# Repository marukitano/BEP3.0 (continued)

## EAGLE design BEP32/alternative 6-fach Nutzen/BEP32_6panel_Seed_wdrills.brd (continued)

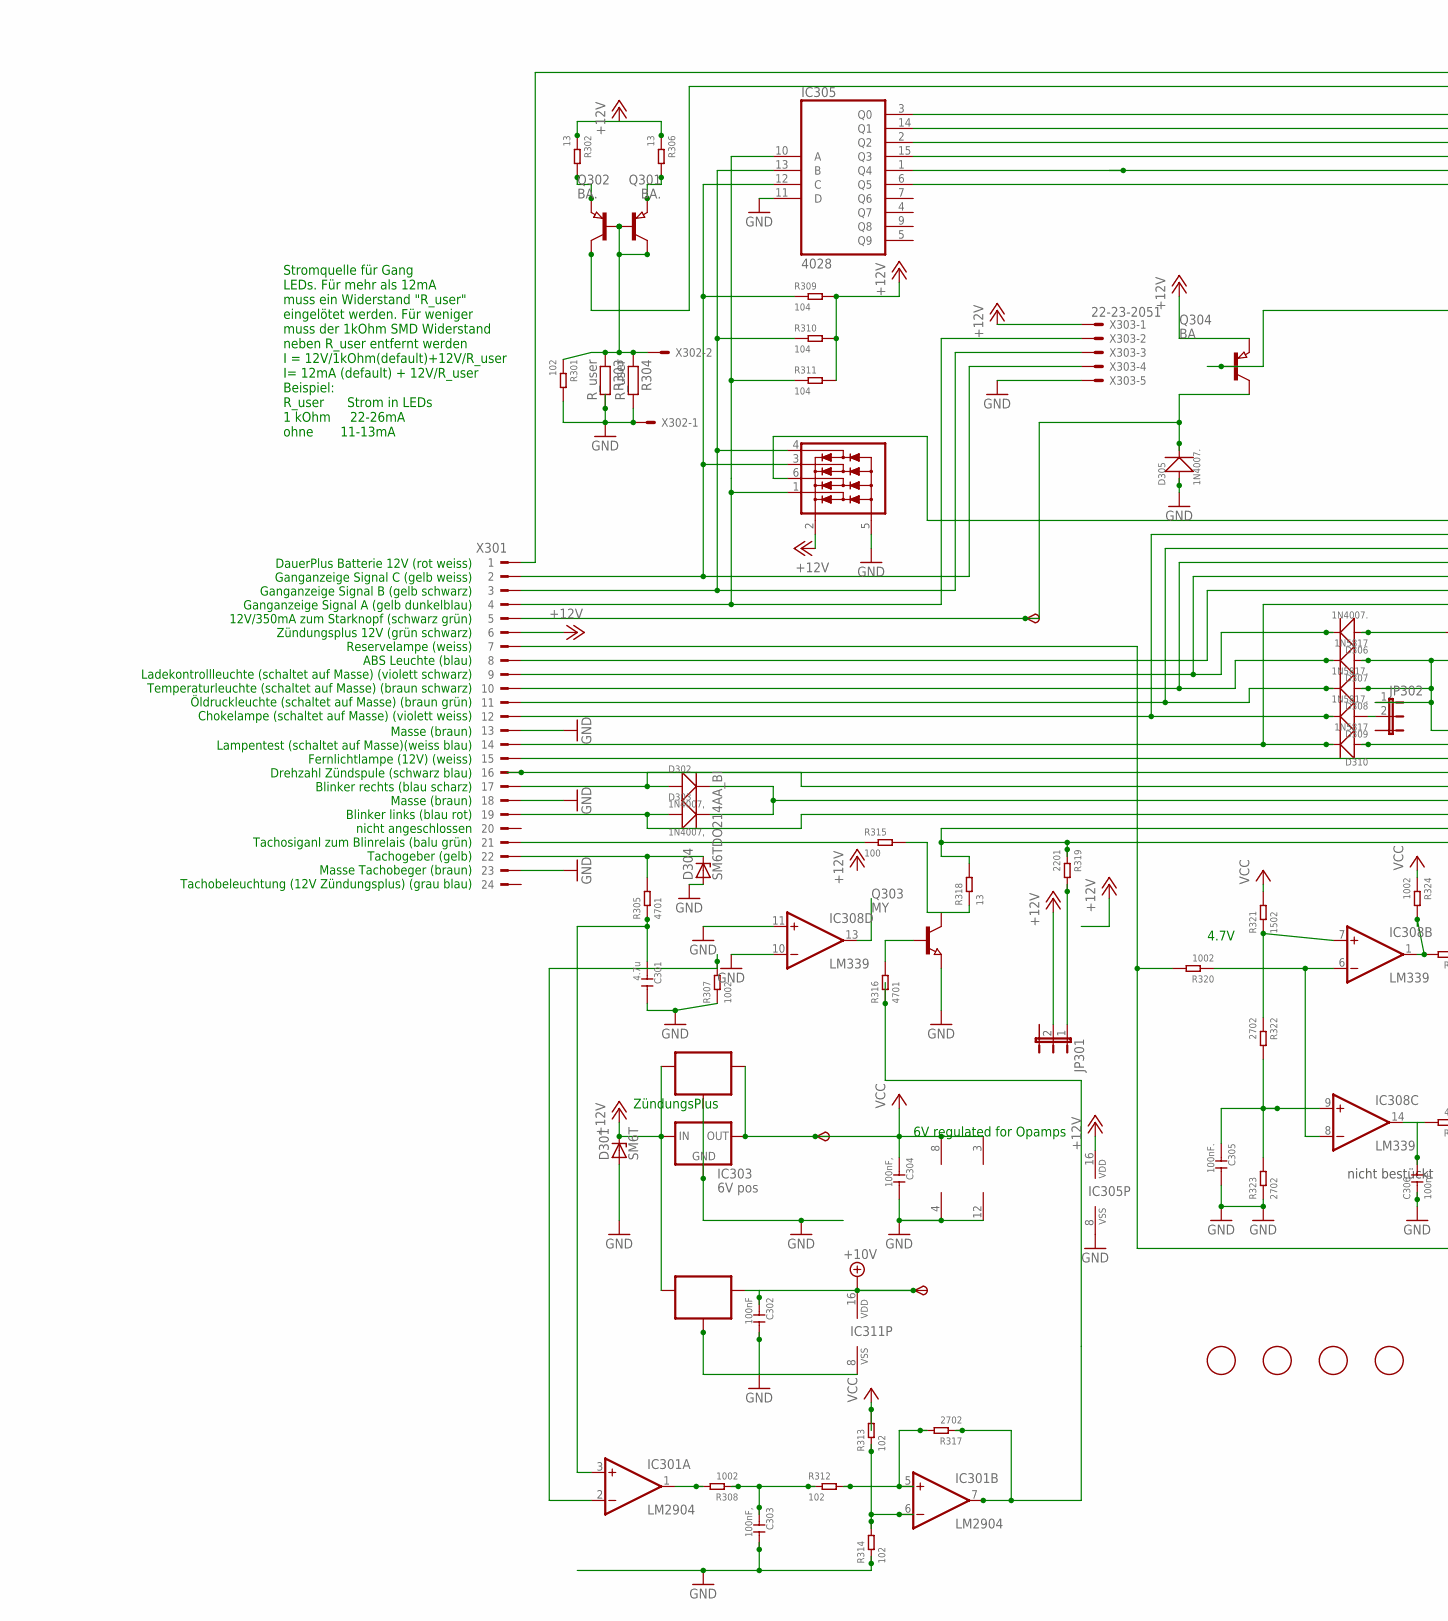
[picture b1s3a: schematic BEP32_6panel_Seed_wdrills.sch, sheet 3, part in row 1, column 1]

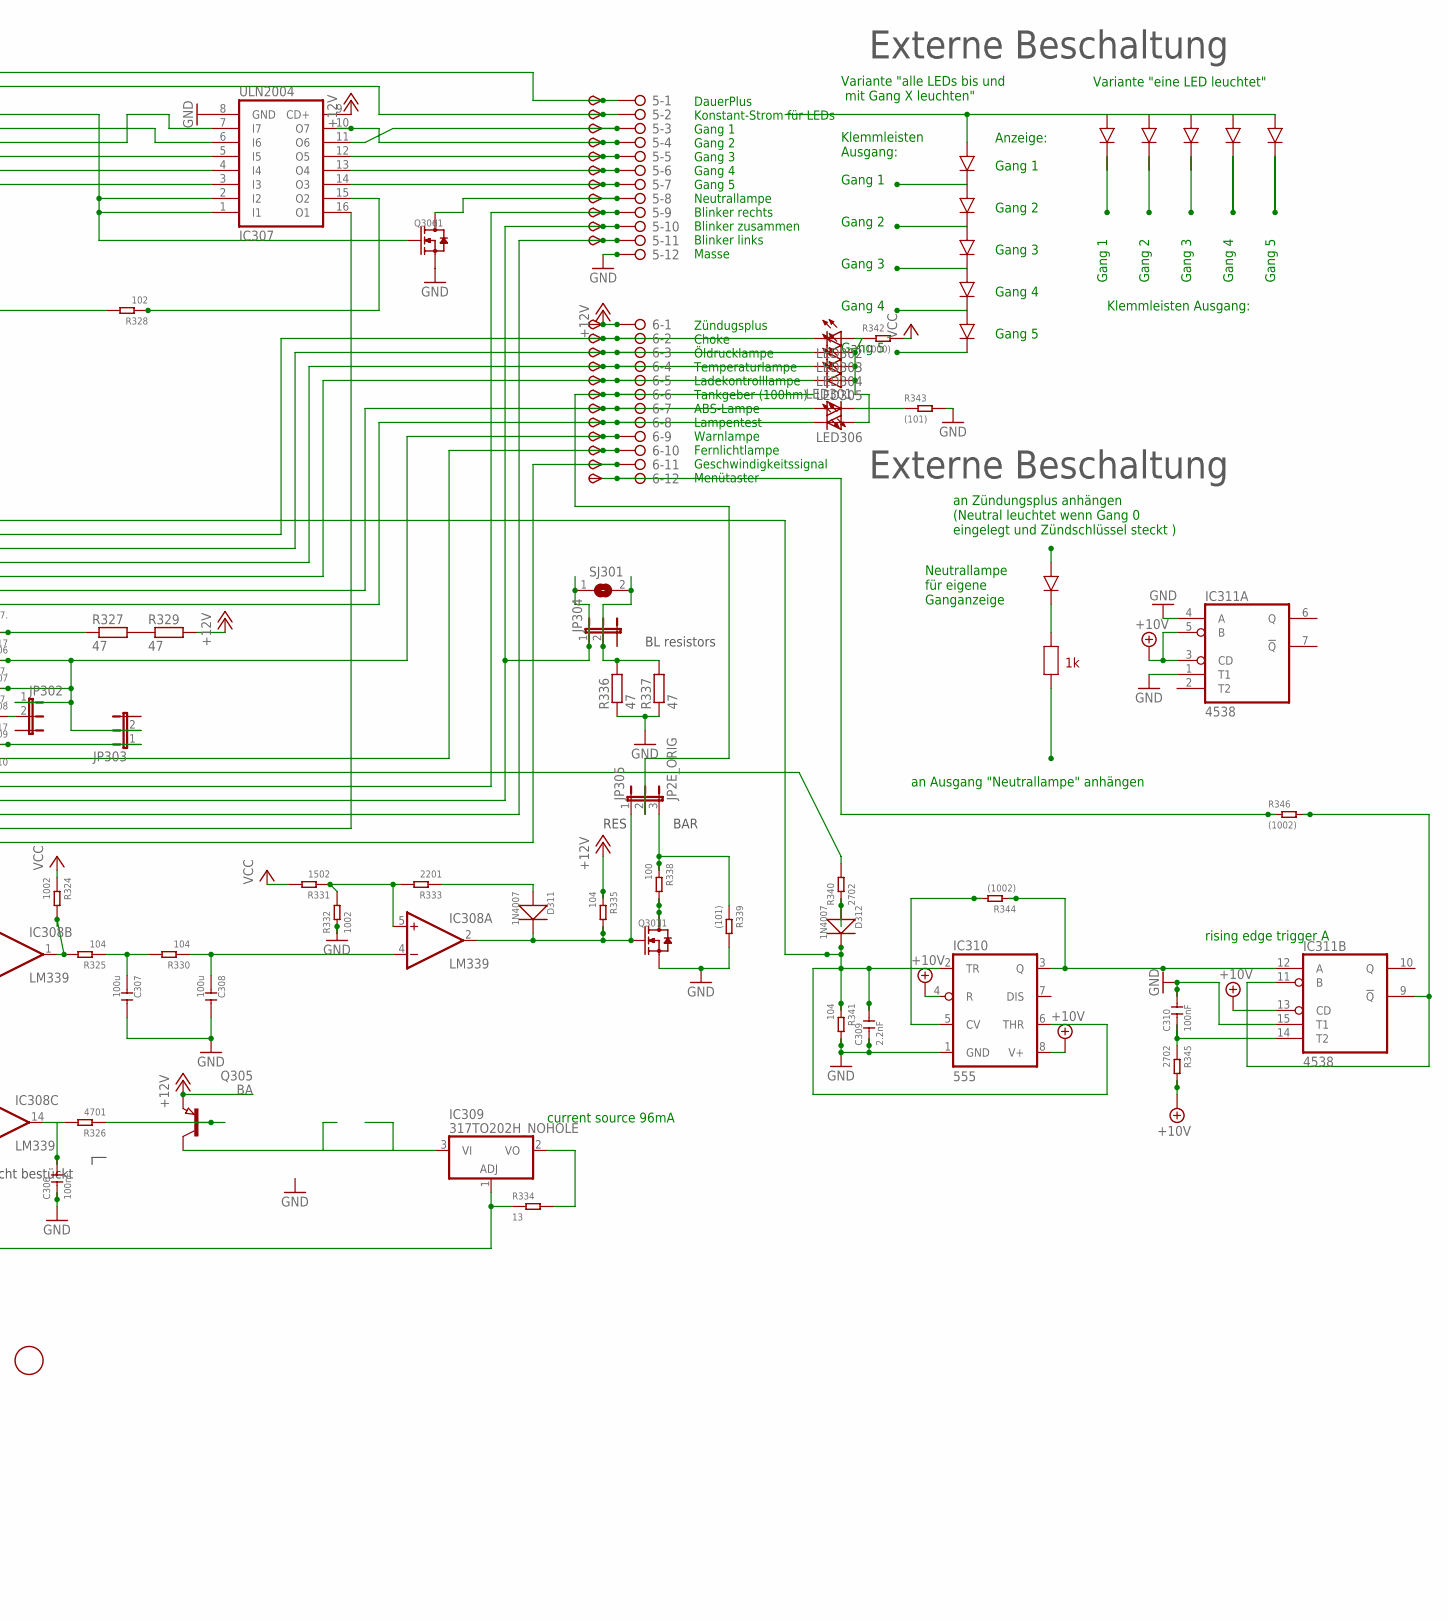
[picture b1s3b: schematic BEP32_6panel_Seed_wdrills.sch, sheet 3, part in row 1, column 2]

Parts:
5, 6: 2081-1132; 12-PIN
6V301, 10V301: TPSB2.0; B2.0
C301: 4.7u; C0805
C302, C310: 100nF; C0805
C303, C304: 100nF,; C0805
C305, C306: 100nF.; C0805
C307, C308: 100u; C1206
C309: 2.2nF; C0805
D301: SM6T; DO214AA
D302, D303: 1N4007,; DO-214AC
D304: SM6TDO214AA_BI; DO214AA_BI
D305, D306: 1N4007.; DO-214AC
D307, D310: 1N5817; DO-214AC_SLIM
D308, D309: 1N5817.; DO-214AC_SLIM
D311, D312: 1N4007; DO-214AC
FID301, FID302, FID303, FID304: FIDUCIAL; FIDUCIAL_1MM
IC301: LM2904; SO08
IC302: 78L06; SOT89_ROUND
IC303: 6V pos; 78LXX
IC304: 78L10; SOT89_ROUND
IC305: 4028; SO16
IC306: NUP4304SOT457_R; SOT457R_PHILIPS
IC307: ULN2004; SO16
IC308: LM339; SO14
IC309: 317TO202H_NOHOLE; TO220H_NOHOLE
IC310: 555; SO08
IC311: 4538; SO16
JP301, JP302, JP303, JP304: JP2EJP2_SMALLPADS; JP2_SMALLPADS
JP305: JP2E_ORIG; JP2_ORIG_SMALLPADS
LED301, LED302, LED303, LED304, LED305, LED306: LEDLD260; LD260
Q301, Q302: BA.; SOT89
Q303: MY; SOT89
Q304, Q305: BA; SOT89
Q306, Q307: J1; SOT-23
R301, R312, R313, R314, R328: 102; R0805
R302, R306, R318, R334: 13; R1206
R303, R304: R_user; R0805
R305, R316, R326: 4701; R0805
R307, R308, R320, R324, R332: 1002; R0805
R309, R310, R311, R325, R330, R335, R341: 104; R0805
R315, R338: 100; R0805
R317, R322, R323, R340, R345: 2702; R0805
R319, R333: 2201; R0805
R321, R331: 1502; R0805
R327, R329, R336, R337: 47; V235/17_1MM
R339, R343: (101); R0805
R342: (1000); R0805
R344, R346: (1002); R0805
SJ301: SJ
START301: TPSB2.0; B2.0
TP47, TP48, TP49, TP50, TP51, TP52, TP53, TP54, TP55, TP56, TP57, TP58, TP59, TP60, TP61, TP62, TP63, TP64, TP66, TP67, TP68, TP69: TPSB2.0; B2.0
TP65: TPSB1,27; B1,27
X301: CON_BMWV2; 24-PIN_V2
X302: 22-23-2021
X303: 22-23-2051

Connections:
+10V: 10V301.TP, C302.1, IC304.1 (OUT), IC310.4 (R), IC310.8 (V+), IC311.3 (CD), IC311.5 (B), IC311.13 (CD), IC311.16 (VDD), R345.2; also elsewhere on the board
+12V: 6.1, D301.C, IC302.3 (IN), IC303.IN, IC304.3 (IN), IC305.16 (VDD), IC306.2 (V+), IC307.9 (CD+), JP301.2, Q304.3 (E), Q305.3 (E), R302.1, R306.1, R309.2, R310.2, R311.2, R329.2, R335.1, TP68.TP, X301.6, X303.1; also elsewhere on the board
+12V3: IC301.7 (OUT), R316.1, R317.1
GND: 5.12, C301.2, C302.2, C303.2, C304.2, C305.2, C306.1, C307.2, C308.2, C309.1, C310.2, D301.A, D304.A, D305.1 (+), IC301.4 (V-), IC302.2 (GND), IC302.2@1 (GND), IC303.GND, IC304.2 (GND), IC304.2@1 (GND), IC305.8 (VSS), IC305.11 (D), IC306.5 (V-), IC307.8 (GND), IC308.10 (-IN), IC308.11 (+IN), IC308.12 (GND), IC310.1 (GND), IC311.1 (T1), IC311.4 (A), IC311.8 (VSS), IC311.15 (T1), Q303.3 (E), Q306.2 (S), Q307.2 (S), R301.2, R303.2, R304.2, R307.1, R314.1, R323.1, R332.1, R336.1, R337.1, R339.2, R341.2, R343.2, X301.13, X301.18, X301.23, X302.1, X303.5; also elsewhere on the board
unnamed: R327.2, R329.1
unnamed: 6.9, D307.1 (+), D308.1 (+), JP302.1, JP303.2, TP65.TP
unnamed: IC305.10 (A), IC306.1 (D1), R311.1, X301.4, X303.2
unnamed: IC305.13 (B), IC306.4 (D4), R310.1, X301.3, X303.3
unnamed: D305.2 (-), Q304.2 (C), START301.TP, X301.5
unnamed: IC305.12 (C), IC306.3 (D3), R309.1, X301.2, X303.4
unnamed: 6.7, LED301.A, TP63.TP, X301.8
unnamed: 6.2, D309.2 (-), LED302.K (C), TP58.TP, X301.12
unnamed: 6.3, D308.2 (-), LED303.K (C), TP59.TP, X301.11
unnamed: 6.4, D307.2 (-), LED304.K (C), TP60.TP, X301.10
unnamed: 6.8, D310.2 (-), LED306.K (C), TP64.TP, X301.14
unnamed: 5.9, D302.1 (+), TP55.TP, X301.17
unnamed: 5.11, D303.1 (+), TP57.TP, X301.19
unnamed: D304.C, R305.2, X301.22
unnamed: C301.1, IC301.3 (+IN), R305.1
unnamed: 6.11, IC307.16 (O1), R318.2, R319.1, TP67.TP
unnamed: IC308.1 (OUT), R324.2, R325.2
unnamed: C307.1, R325.1, R330.2
unnamed: C308.1, IC308.4 (-IN), R330.1
unnamed: IC308.5 (+IN), R331.1, R332.2, R333.2
unnamed: D311.1 (+), R333.1
unnamed: C305.1, IC308.9 (+IN), R322.2, R323.2
unnamed: C306.2, IC308.14 (OUT), R326.2
unnamed: Q305.1 (B), R326.1
unnamed: IC305.2 (Q2), IC307.7 (I7)
unnamed: 5.5, IC307.12 (O5), TP51.TP
unnamed: IC305.1 (Q4), IC307.4 (I4)
unnamed: 5.8, Q306.3 (D), TP54.TP
unnamed: 6.10, TP66.TP, X301.15
unnamed: 6.5, D306.2 (-), LED305.K (C), TP61.TP, X301.9
unnamed: D306.1 (+), R327.1
unnamed: IC305.6 (Q5), IC307.3 (I3)
unnamed: 5.4, IC307.10 (O7), TP50.TP
unnamed: IC309.1 (ADJ), R320.2, R334.1, X301.7
unnamed: IC308.6 (-IN), IC308.8 (-IN), R320.1
unnamed: 5.2, Q301.2 (C), TP48.TP
unnamed: 5.1, TP47.TP, X301.1
unnamed: R340.2, X301.16
unnamed: IC305.15 (Q3), IC307.5 (I5)
unnamed: 5.6, IC307.13 (O4), TP52.TP
unnamed: 5.7, IC307.14 (O3), TP53.TP
unnamed: 6.6, JP305.2, TP62.TP
unnamed: LED301.K (C), R343.1
unnamed: LED302.A, LED303.A, LED304.A, LED305.A, LED306.A, R342.1
unnamed: Q304.1 (B), R328.2
unnamed: IC305.3 (Q0), IC307.1 (I1), IC307.2 (I2), Q306.1 (G)
unnamed: IC305.14 (Q1), IC307.6 (I6)
unnamed: 5.3, IC307.11 (O6), TP49.TP
unnamed: Q301.1 (B), Q302.1 (B), Q302.2 (C), R301.1, R303.1, R304.1, X302.2
unnamed: Q301.3 (E), R302.2
unnamed: Q302.3 (E), R306.2
unnamed: IC308.7 (+IN), R321.1, R322.1
unnamed: IC301.2 (-IN), R307.2
unnamed: Q303.1 (B), R316.2
unnamed: Q307.3 (D), R338.2
unnamed: IC309.2 (VO), R334.2
unnamed: IC309.3 (VI), Q305.2 (C)
unnamed: C309.2, D312.2 (-), IC306.6 (D2), IC310.2 (TR), IC310.6 (THR), R341.1
unnamed: IC310.5 (CV), R344.2
unnamed: IC310.3 (Q), IC311.12 (A), R344.1
unnamed: D312.1 (+), R340.1
unnamed: 5.10, D302.2 (-), D303.2 (-), JP304.1, SJ301.1, TP56.TP
unnamed: JP304.2, R336.2, R337.2, SJ301.2
unnamed: IC311.9 (!Q), IC311.11 (B), R346.2
unnamed: C310.1, IC311.14 (T2), R345.1
unnamed: JP301.1, R319.2
unnamed: IC307.15 (O2), R328.1
unnamed: 6.12, R346.1, TP69.TP
unnamed: D309.1 (+), JP302.2
unnamed: D311.2 (-), IC308.2 (OUT), JP305.1, Q307.1 (G), R335.2
unnamed: IC301.1 (OUT), R308.2
unnamed: C303.1, R308.1, R312.1
unnamed: IC301.5 (+IN), R312.2, R317.2
unnamed: IC301.6 (-IN), R313.1, R314.2
unnamed: D310.1 (+), JP303.1
unnamed: JP305.3, R338.1, R339.1
unnamed: R315.1, X301.21
unnamed: Q303.2 (C), R315.2, R318.1
VCC: 6V301.TP, C304.1, IC301.8 (V+), IC302.1 (OUT), IC303.OUT, IC308.3 (V+), R313.2, R321.2, R324.1, R331.2, R342.2; also elsewhere on the board

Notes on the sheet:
6V regulated for Opamps
current source 96mA
ZündungsPlus
Zündugsplus Choke Öldrucklampe Temperaturlampe Ladekontrolllampe Tankgeber (100hm) ABS-Lampe Lampentest Warnlampe Fernlichtlampe Geschwindigkeitssignal Menütaster
DauerPlus Konstant-Strom für LEDs Gang 1 Gang 2 Gang 3 Gang 4 Gang 5 Neutrallampe Blinker rechts Blinker zusammen Blinker links Masse
DauerPlus Batterie 12V (rot weiss) Ganganzeige Signal C (gelb weiss) Ganganzeige Signal B (gelb schwarz) Ganganzeige Signal A (gelb dunkelblau) 12V/350mA zum Starknopf (schwarz grün) Zündungsplus 12V (grün schwarz) Reservelampe (weiss) ABS Leuchte (blau) Ladekontrollleuchte (schaltet auf Masse) (vi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
Masse (braun) Lampentest (schaltet auf Masse)(weiss blau) Fernlichtlampe (12V) (weiss) Drehzahl Zündspule (schwarz blau) Blinker rechts (blau scharz) Masse (braun) Blinker links (blau rot) nicht angeschlossen Tachosiganl zum Blinrelais (balu grün) Tachogeber (gelb) Masse Tachobeger (braun) Tachobel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
4.7V
Stromquelle für Gang LEDs. Für mehr als 12mA muss ein Widerstand "R_user" eingelötet werden. Für weniger muss der 1kOhm SMD Widerstand neben R_user entfernt werden I = 12V/1kOhm(default)+12V/R_user I= 12mA (default) + 12V/R_user Beispiel: R_user Strom in LEDs 1 kOhm 22-26mA ohne 11-13mA
Gang 1
Gang 2
Gang 3
Gang 4
Gang 5
Variante "eine LED leuchtet"
Variante "alle LEDs bis und mit Gang X leuchten"
Klemmleisten Ausgang:
Klemmleisten Ausgang:
an Zündungsplus anhängen (Neutral leuchtet wenn Gang 0 eingelegt und Zündschlüssel steckt )
an Ausgang "Neutrallampe" anhängen
Neutrallampe für eigene Ganganzeige
Externe Beschaltung
Anzeige:
nicht bestückt
rising edge trigger A
BAR
RES
BL resistors

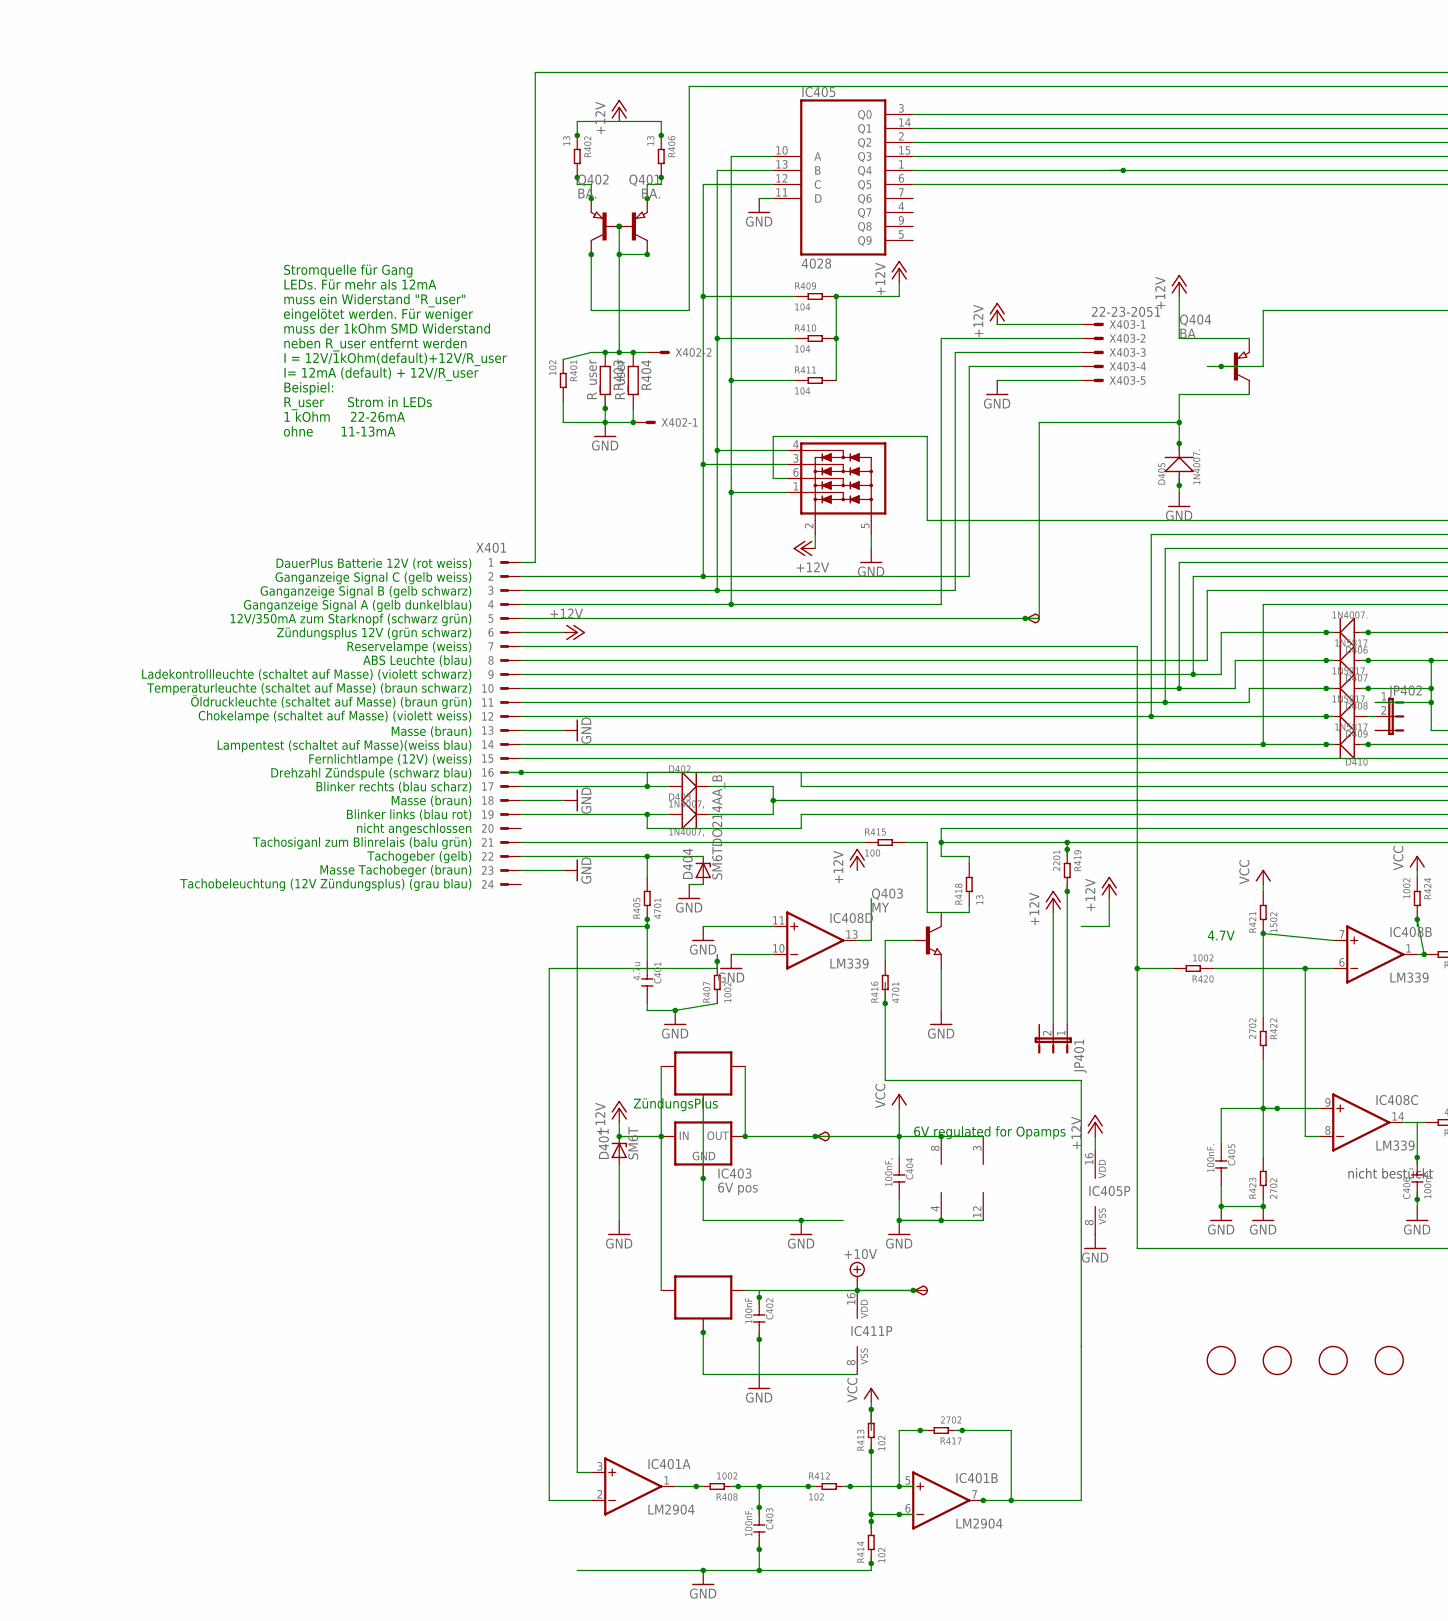
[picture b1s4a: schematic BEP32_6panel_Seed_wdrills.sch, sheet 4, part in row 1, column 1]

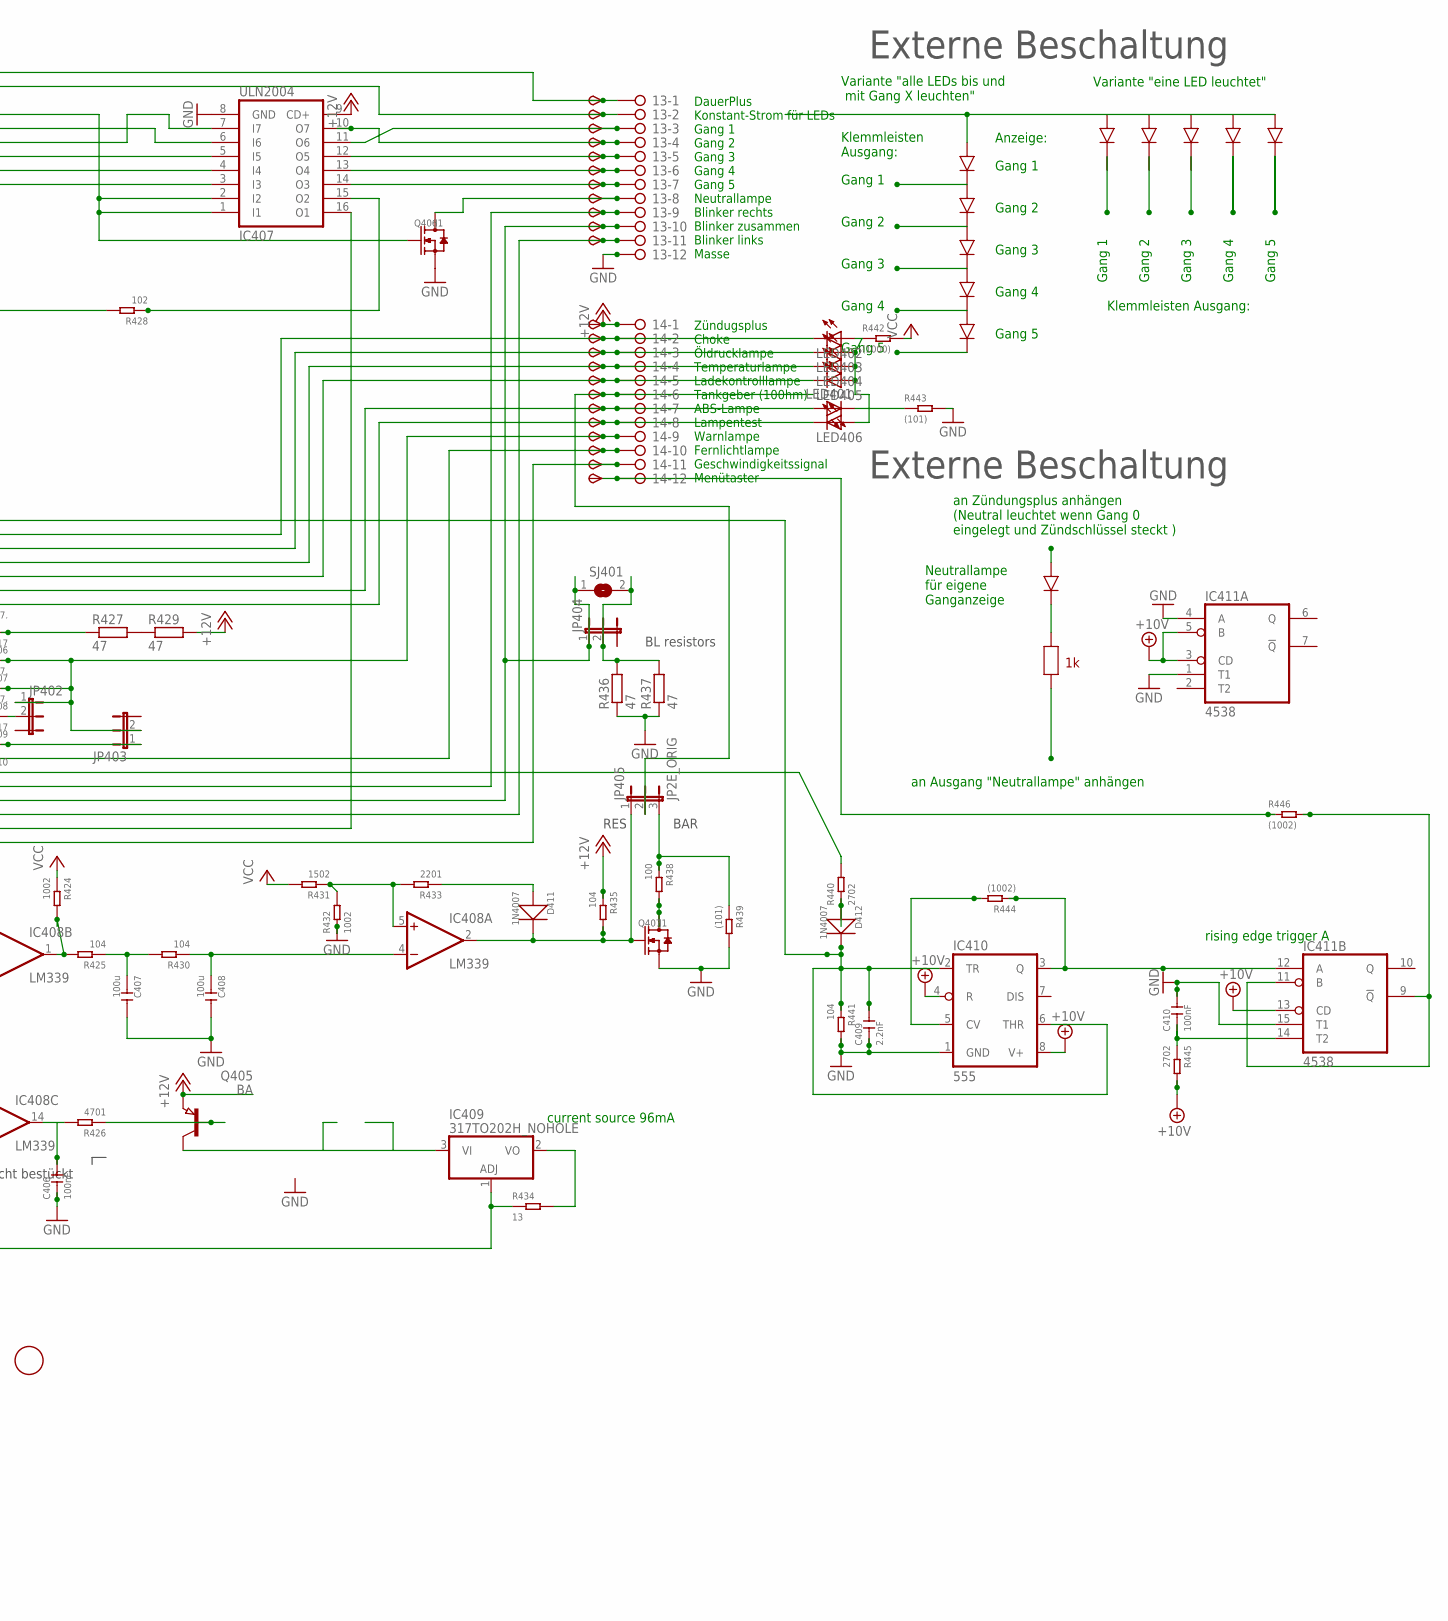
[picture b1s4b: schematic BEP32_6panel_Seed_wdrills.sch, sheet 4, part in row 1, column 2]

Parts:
6V401, 10V401: TPSB2.0; B2.0
13, 14: 2081-1132; 12-PIN
C401: 4.7u; C0805
C402, C410: 100nF; C0805
C403, C404: 100nF,; C0805
C405, C406: 100nF.; C0805
C407, C408: 100u; C1206
C409: 2.2nF; C0805
D401: SM6T; DO214AA
D402, D403: 1N4007,; DO-214AC
D404: SM6TDO214AA_BI; DO214AA_BI
D405, D406: 1N4007.; DO-214AC
D407, D410: 1N5817; DO-214AC_SLIM
D408, D409: 1N5817.; DO-214AC_SLIM
D411, D412: 1N4007; DO-214AC
FID401, FID402, FID403, FID404: FIDUCIAL; FIDUCIAL_1MM
IC401: LM2904; SO08
IC402: 78L06; SOT89_ROUND
IC403: 6V pos; 78LXX
IC404: 78L10; SOT89_ROUND
IC405: 4028; SO16
IC406: NUP4304SOT457_R; SOT457R_PHILIPS
IC407: ULN2004; SO16
IC408: LM339; SO14
IC409: 317TO202H_NOHOLE; TO220H_NOHOLE
IC410: 555; SO08
IC411: 4538; SO16
JP401, JP402, JP403, JP404: JP2EJP2_SMALLPADS; JP2_SMALLPADS
JP405: JP2E_ORIG; JP2_ORIG_SMALLPADS
LED401, LED402, LED403, LED404, LED405, LED406: LEDLD260; LD260
Q401, Q402: BA.; SOT89
Q403: MY; SOT89
Q404, Q405: BA; SOT89
Q406, Q407: J1; SOT-23
R401, R412, R413, R414, R428: 102; R0805
R402, R406, R418, R434: 13; R1206
R403, R404: R_user; R0805
R405, R416, R426: 4701; R0805
R407, R408, R420, R424, R432: 1002; R0805
R409, R410, R411, R425, R430, R435, R441: 104; R0805
R415, R438: 100; R0805
R417, R422, R423, R440, R445: 2702; R0805
R419, R433: 2201; R0805
R421, R431: 1502; R0805
R427, R429, R436, R437: 47; V235/17_1MM
R439, R443: (101); R0805
R442: (1000); R0805
R444, R446: (1002); R0805
SJ401: SJ
START401: TPSB2.0; B2.0
TP139, TP140, TP141, TP142, TP143, TP144, TP145, TP146, TP147, TP148, TP149, TP150, TP151, TP152, TP153, TP154, TP155, TP156, TP158, TP159, TP160, TP161: TPSB2.0; B2.0
TP157: TPSB1,27; B1,27
X401: CON_BMWV2; 24-PIN_V2
X402: 22-23-2021
X403: 22-23-2051

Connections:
+10V: 10V401.TP, C402.1, IC404.1 (OUT), IC410.4 (R), IC410.8 (V+), IC411.3 (CD), IC411.5 (B), IC411.13 (CD), IC411.16 (VDD), R445.2; also elsewhere on the board
+12V: 14.1, D401.C, IC402.3 (IN), IC403.IN, IC404.3 (IN), IC405.16 (VDD), IC406.2 (V+), IC407.9 (CD+), JP401.2, Q404.3 (E), Q405.3 (E), R402.1, R406.1, R409.2, R410.2, R411.2, R429.2, R435.1, TP160.TP, X401.6, X403.1; also elsewhere on the board
+12V7: IC401.7 (OUT), R416.1, R417.1
GND: 13.12, C401.2, C402.2, C403.2, C404.2, C405.2, C406.1, C407.2, C408.2, C409.1, C410.2, D401.A, D404.A, D405.1 (+), IC401.4 (V-), IC402.2 (GND), IC402.2@1 (GND), IC403.GND, IC404.2 (GND), IC404.2@1 (GND), IC405.8 (VSS), IC405.11 (D), IC406.5 (V-), IC407.8 (GND), IC408.10 (-IN), IC408.11 (+IN), IC408.12 (GND), IC410.1 (GND), IC411.1 (T1), IC411.4 (A), IC411.8 (VSS), IC411.15 (T1), Q403.3 (E), Q406.2 (S), Q407.2 (S), R401.2, R403.2, R404.2, R407.1, R414.1, R423.1, R432.1, R436.1, R437.1, R439.2, R441.2, R443.2, X401.13, X401.18, X401.23, X402.1, X403.5; also elsewhere on the board
unnamed: R427.2, R429.1
unnamed: 14.9, D407.1 (+), D408.1 (+), JP402.1, JP403.2, TP157.TP
unnamed: IC405.10 (A), IC406.1 (D1), R411.1, X401.4, X403.2
unnamed: IC405.13 (B), IC406.4 (D4), R410.1, X401.3, X403.3
unnamed: D405.2 (-), Q404.2 (C), START401.TP, X401.5
unnamed: IC405.12 (C), IC406.3 (D3), R409.1, X401.2, X403.4
unnamed: 14.7, LED401.A, TP155.TP, X401.8
unnamed: 14.2, D409.2 (-), LED402.K (C), TP150.TP, X401.12
unnamed: 14.3, D408.2 (-), LED403.K (C), TP151.TP, X401.11
unnamed: 14.4, D407.2 (-), LED404.K (C), TP152.TP, X401.10
unnamed: 14.8, D410.2 (-), LED406.K (C), TP156.TP, X401.14
unnamed: 13.9, D402.1 (+), TP147.TP, X401.17
unnamed: 13.11, D403.1 (+), TP149.TP, X401.19
unnamed: D404.C, R405.2, X401.22
unnamed: C401.1, IC401.3 (+IN), R405.1
unnamed: 14.11, IC407.16 (O1), R418.2, R419.1, TP159.TP
unnamed: IC408.1 (OUT), R424.2, R425.2
unnamed: C407.1, R425.1, R430.2
unnamed: C408.1, IC408.4 (-IN), R430.1
unnamed: IC408.5 (+IN), R431.1, R432.2, R433.2
unnamed: D411.1 (+), R433.1
unnamed: C405.1, IC408.9 (+IN), R422.2, R423.2
unnamed: C406.2, IC408.14 (OUT), R426.2
unnamed: Q405.1 (B), R426.1
unnamed: IC405.2 (Q2), IC407.7 (I7)
unnamed: 13.5, IC407.12 (O5), TP143.TP
unnamed: IC405.1 (Q4), IC407.4 (I4)
unnamed: 13.8, Q406.3 (D), TP146.TP
unnamed: 14.10, TP158.TP, X401.15
unnamed: 14.5, D406.2 (-), LED405.K (C), TP153.TP, X401.9
unnamed: D406.1 (+), R427.1
unnamed: IC405.6 (Q5), IC407.3 (I3)
unnamed: 13.4, IC407.10 (O7), TP142.TP
unnamed: IC409.1 (ADJ), R420.2, R434.1, X401.7
unnamed: IC408.6 (-IN), IC408.8 (-IN), R420.1
unnamed: 13.2, Q401.2 (C), TP140.TP
unnamed: 13.1, TP139.TP, X401.1
unnamed: R440.2, X401.16
unnamed: IC405.15 (Q3), IC407.5 (I5)
unnamed: 13.6, IC407.13 (O4), TP144.TP
unnamed: 13.7, IC407.14 (O3), TP145.TP
unnamed: 14.6, JP405.2, TP154.TP
unnamed: LED401.K (C), R443.1
unnamed: LED402.A, LED403.A, LED404.A, LED405.A, LED406.A, R442.1
unnamed: Q404.1 (B), R428.2
unnamed: IC405.3 (Q0), IC407.1 (I1), IC407.2 (I2), Q406.1 (G)
unnamed: IC405.14 (Q1), IC407.6 (I6)
unnamed: 13.3, IC407.11 (O6), TP141.TP
unnamed: Q401.1 (B), Q402.1 (B), Q402.2 (C), R401.1, R403.1, R404.1, X402.2
unnamed: Q401.3 (E), R402.2
unnamed: Q402.3 (E), R406.2
unnamed: IC408.7 (+IN), R421.1, R422.1
unnamed: IC401.2 (-IN), R407.2
unnamed: Q403.1 (B), R416.2
unnamed: Q407.3 (D), R438.2
unnamed: IC409.2 (VO), R434.2
unnamed: IC409.3 (VI), Q405.2 (C)
unnamed: C409.2, D412.2 (-), IC406.6 (D2), IC410.2 (TR), IC410.6 (THR), R441.1
unnamed: IC410.5 (CV), R444.2
unnamed: IC410.3 (Q), IC411.12 (A), R444.1
unnamed: D412.1 (+), R440.1
unnamed: 13.10, D402.2 (-), D403.2 (-), JP404.1, SJ401.1, TP148.TP
unnamed: JP404.2, R436.2, R437.2, SJ401.2
unnamed: IC411.9 (!Q), IC411.11 (B), R446.2
unnamed: C410.1, IC411.14 (T2), R445.1
unnamed: JP401.1, R419.2
unnamed: IC407.15 (O2), R428.1
unnamed: 14.12, R446.1, TP161.TP
unnamed: D409.1 (+), JP402.2
unnamed: D411.2 (-), IC408.2 (OUT), JP405.1, Q407.1 (G), R435.2
unnamed: IC401.1 (OUT), R408.2
unnamed: C403.1, R408.1, R412.1
unnamed: IC401.5 (+IN), R412.2, R417.2
unnamed: IC401.6 (-IN), R413.1, R414.2
unnamed: D410.1 (+), JP403.1
unnamed: JP405.3, R438.1, R439.1
unnamed: R415.1, X401.21
unnamed: Q403.2 (C), R415.2, R418.1
VCC: 6V401.TP, C404.1, IC401.8 (V+), IC402.1 (OUT), IC403.OUT, IC408.3 (V+), R413.2, R421.2, R424.1, R431.2, R442.2; also elsewhere on the board

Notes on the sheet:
6V regulated for Opamps
current source 96mA
ZündungsPlus
Zündugsplus Choke Öldrucklampe Temperaturlampe Ladekontrolllampe Tankgeber (100hm) ABS-Lampe Lampentest Warnlampe Fernlichtlampe Geschwindigkeitssignal Menütaster
DauerPlus Konstant-Strom für LEDs Gang 1 Gang 2 Gang 3 Gang 4 Gang 5 Neutrallampe Blinker rechts Blinker zusammen Blinker links Masse
DauerPlus Batterie 12V (rot weiss) Ganganzeige Signal C (gelb weiss) Ganganzeige Signal B (gelb schwarz) Ganganzeige Signal A (gelb dunkelblau) 12V/350mA zum Starknopf (schwarz grün) Zündungsplus 12V (grün schwarz) Reservelampe (weiss) ABS Leuchte (blau) Ladekontrollleuchte (schaltet auf Masse) (vi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
Masse (braun) Lampentest (schaltet auf Masse)(weiss blau) Fernlichtlampe (12V) (weiss) Drehzahl Zündspule (schwarz blau) Blinker rechts (blau scharz) Masse (braun) Blinker links (blau rot) nicht angeschlossen Tachosiganl zum Blinrelais (balu grün) Tachogeber (gelb) Masse Tachobeger (braun) Tachobel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
4.7V
Stromquelle für Gang LEDs. Für mehr als 12mA muss ein Widerstand "R_user" eingelötet werden. Für weniger muss der 1kOhm SMD Widerstand neben R_user entfernt werden I = 12V/1kOhm(default)+12V/R_user I= 12mA (default) + 12V/R_user Beispiel: R_user Strom in LEDs 1 kOhm 22-26mA ohne 11-13mA
Gang 1
Gang 2
Gang 3
Gang 4
Gang 5
Variante "eine LED leuchtet"
Variante "alle LEDs bis und mit Gang X leuchten"
Klemmleisten Ausgang:
Klemmleisten Ausgang:
an Zündungsplus anhängen (Neutral leuchtet wenn Gang 0 eingelegt und Zündschlüssel steckt )
an Ausgang "Neutrallampe" anhängen
Neutrallampe für eigene Ganganzeige
Externe Beschaltung
Anzeige:
nicht bestückt
rising edge trigger A
BAR
RES
BL resistors
